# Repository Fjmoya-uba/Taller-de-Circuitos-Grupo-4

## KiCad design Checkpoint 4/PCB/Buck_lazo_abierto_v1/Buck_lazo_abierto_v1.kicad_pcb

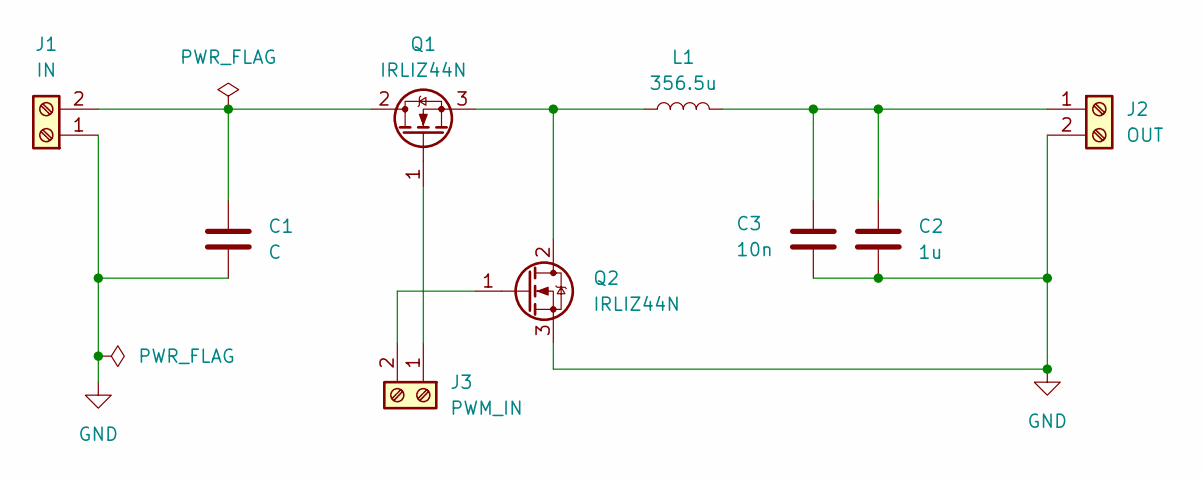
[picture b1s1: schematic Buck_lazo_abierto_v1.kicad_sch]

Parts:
C1: C; C_Radial_D12.5mm_H20.0mm_P5.00mm
C2: 1u; C_Radial_D12.5mm_H20.0mm_P5.00mm
C3: 10n; C_Disc_D10.0mm_W2.5mm_P5.00mm
J1: IN; TerminalBlock_MaiXu_MX126-5.0-02P_1x02_P5.00mm
J2: OUT; TerminalBlock_MaiXu_MX126-5.0-02P_1x02_P5.00mm
J3: PWM_IN; TerminalBlock_MaiXu_MX126-5.0-02P_1x02_P5.00mm
L1: 356.5u; L_Toroid_Vertical_L46.0mm_W19.1mm_P21.80mm_Bourns_5700
Q1, Q2: IRLIZ44N; TO-220F-3_Vertical

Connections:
GND: C1.2, C2.2, C3.2, J1.1, J2.2, Q2.3 (S)
unnamed: C1.1, J1.2, Q1.2 (D)
unnamed: C2.1, C3.1, J2.1, L1.2
unnamed: J3.1, Q1.1 (G)
unnamed: J3.2, Q2.1 (G)
unnamed: L1.1, Q1.3 (S), Q2.2 (D)

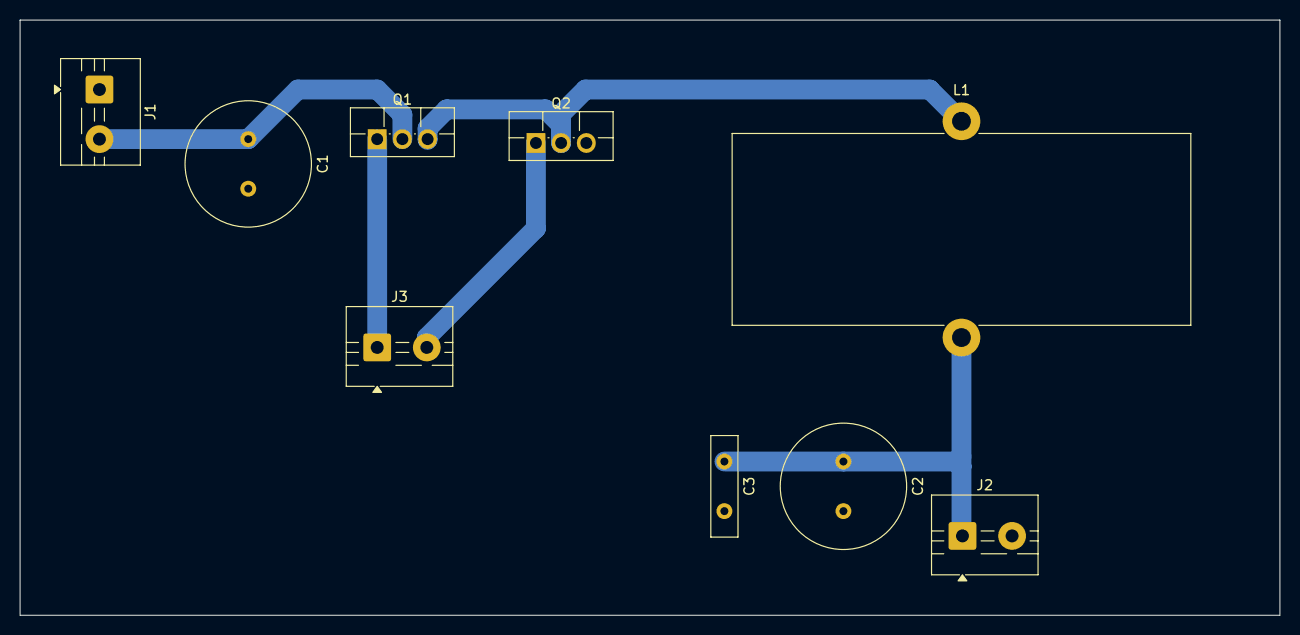
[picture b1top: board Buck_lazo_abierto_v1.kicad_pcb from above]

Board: 2 copper layers, 127.0 x 60.0 mm, 9 parts (0 on the bottom side), 6 nets.

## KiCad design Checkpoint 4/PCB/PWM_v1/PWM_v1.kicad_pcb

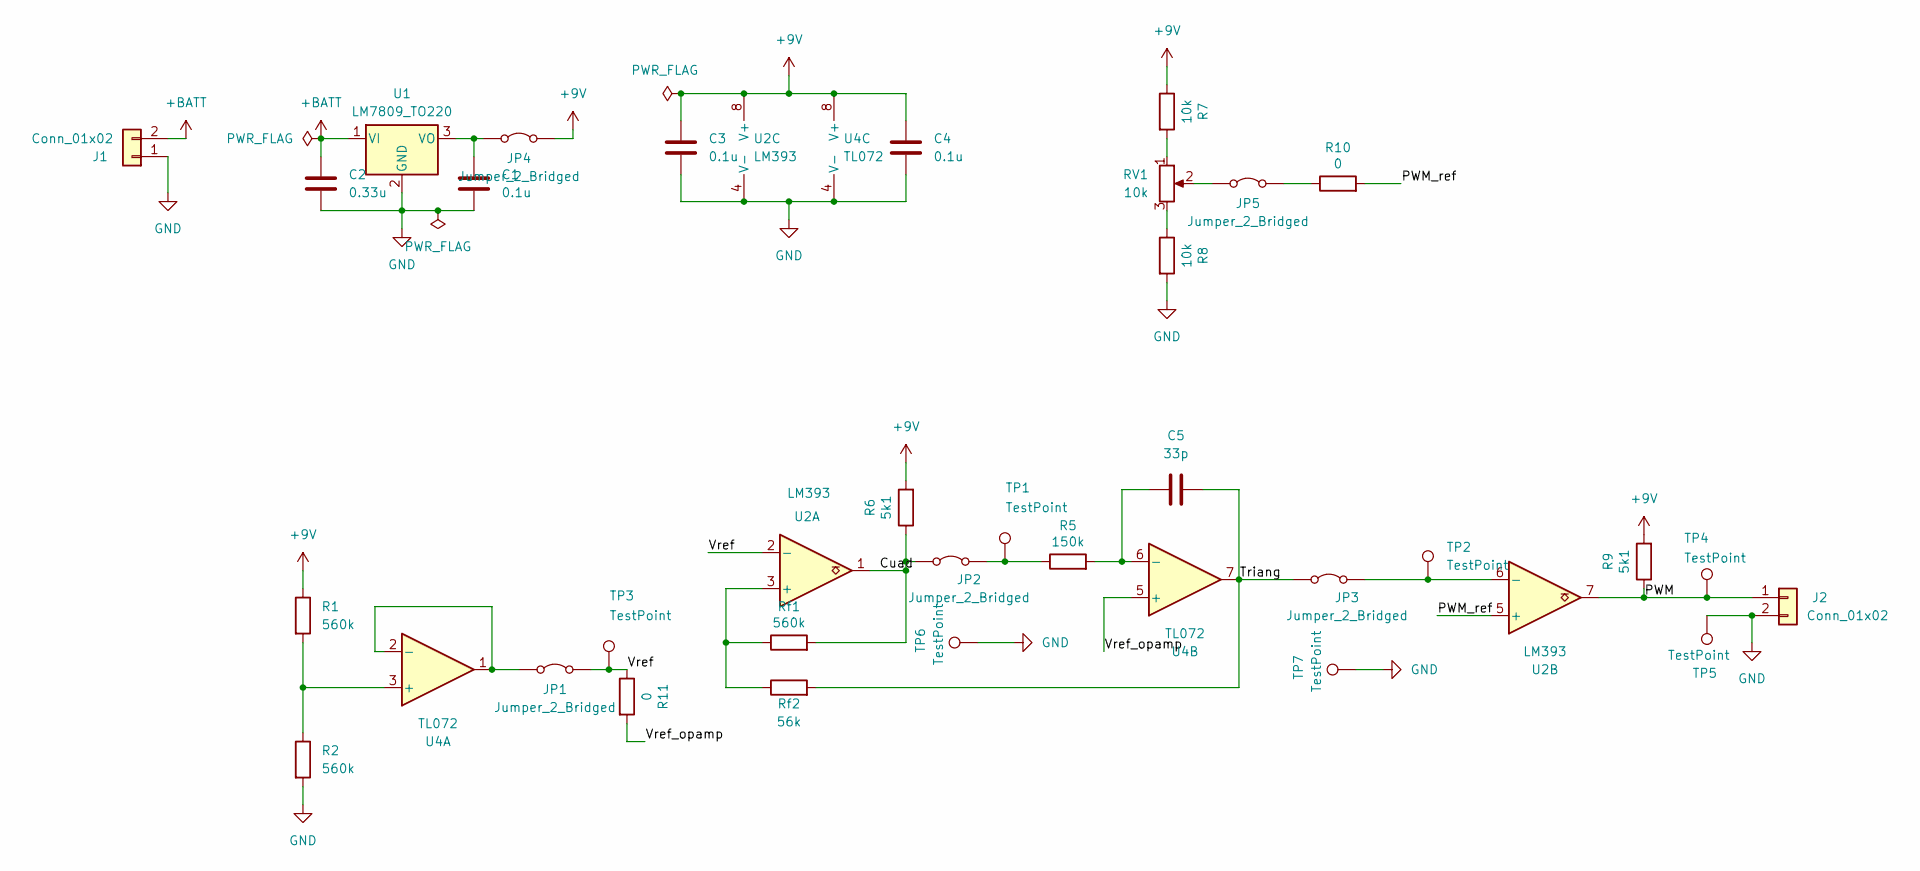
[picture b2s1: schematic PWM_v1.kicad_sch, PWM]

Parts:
C1, C3, C4: 0.1u; C_Disc_D5.0mm_W2.5mm_P2.50mm
C2: 0.33u; C_Disc_D5.0mm_W2.5mm_P2.50mm
C5: 33p; C_Disc_D5.0mm_W2.5mm_P2.50mm
J1, J2: Conn_01x02; TerminalBlock_MaiXu_MX126-5.0-02P_1x02_P5.00mm
JP1, JP2, JP3, JP4, JP5: Jumper_2_Bridged; PinHeader_1x02_P2.54mm_Vertical
R1, R2: 560k; R_Axial_DIN0207_L6.3mm_D2.5mm_P7.62mm_Horizontal
R5: 150k; R_Axial_DIN0207_L6.3mm_D2.5mm_P7.62mm_Horizontal
R6, R9: 5k1; R_Axial_DIN0207_L6.3mm_D2.5mm_P7.62mm_Horizontal
R7, R8: 10k; R_Axial_DIN0207_L6.3mm_D2.5mm_P7.62mm_Horizontal
R10, R11: 0; R_Axial_DIN0207_L6.3mm_D2.5mm_P7.62mm_Horizontal
RV1: 10k; Potentiometer_Piher_PC-16_Single_Horizontal
Rf1: 560k; R_Axial_DIN0207_L6.3mm_D2.5mm_P7.62mm_Horizontal
Rf2: 56k; R_Axial_DIN0207_L6.3mm_D2.5mm_P7.62mm_Horizontal
TP1, TP2, TP3: TestPoint
TP4, TP5, TP6, TP7: TestPoint; PinHeader_1x01_P2.54mm_Vertical
U1: LM7809_TO220; TO-220-3_Vertical
U2: LM393; DIP-8_W7.62mm_Socket_LongPads
U4: TL072; DIP-8_W7.62mm_Socket_LongPads

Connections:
+9V: C3.1, C4.1, JP4.2 (B), R1.1, R6.2, R7.1, R9.2, U2.8 (V+), U4.8 (V+)
+BATT: C2.1, J1.2, U1.1 (VI)
/Cuad: JP2.1 (A), R6.1, Rf1.2, U2.1
/PWM: J2.1, R9.1, TP4.1 (1_1), U2.7
/PWM_ref: R10.2, U2.5 (+)
/Triang: C5.1, JP3.1 (A), Rf2.2, U4.7
/Vref: JP1.2 (B), R11.1, TP3.1, U2.2 (-)
/Vref_opamp: R11.2, U4.5 (+)
GND: C1.2, C2.2, C3.2, C4.2, J1.1, J2.2, R2.2, R8.2, TP5.1 (1_1), TP6.1 (1_1), TP7.1 (1_1), U1.2 (GND), U2.4 (V-), U4.4 (V-)
unnamed: JP1.1 (A), U4.1, U4.2 (-)
unnamed: JP2.2 (B), R5.1, TP1.1
unnamed: JP3.2 (B), TP2.1, U2.6 (-)
unnamed: C1.1, JP4.1 (A), U1.3 (VO)
unnamed: JP5.1 (A), RV1.2
unnamed: JP5.2 (B), R10.1
unnamed: R7.2, RV1.1
unnamed: R8.1, RV1.3
unnamed: Rf1.1, Rf2.1, U2.3 (+)
unnamed: R1.2, R2.1, U4.3 (+)
unnamed: C5.2, R5.2, U4.6 (-)

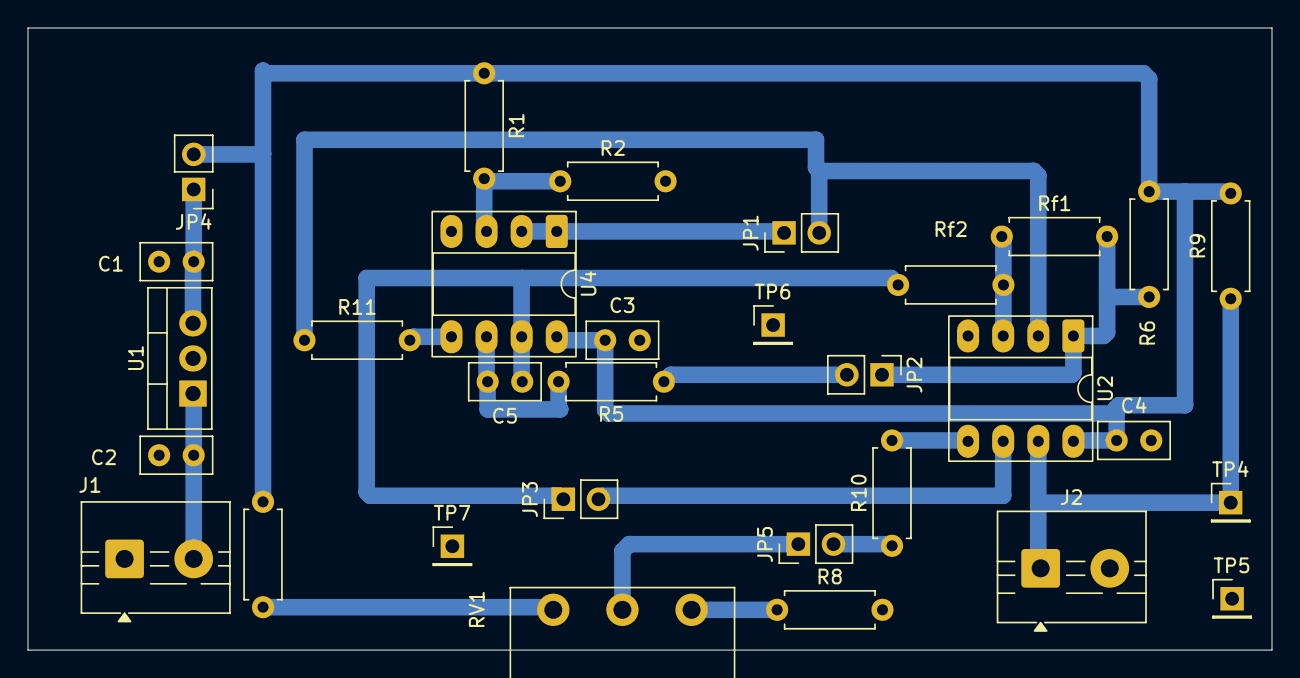
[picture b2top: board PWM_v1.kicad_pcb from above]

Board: 2 copper layers, 90.0 x 45.0 mm, 31 parts (0 on the bottom side), 20 nets.

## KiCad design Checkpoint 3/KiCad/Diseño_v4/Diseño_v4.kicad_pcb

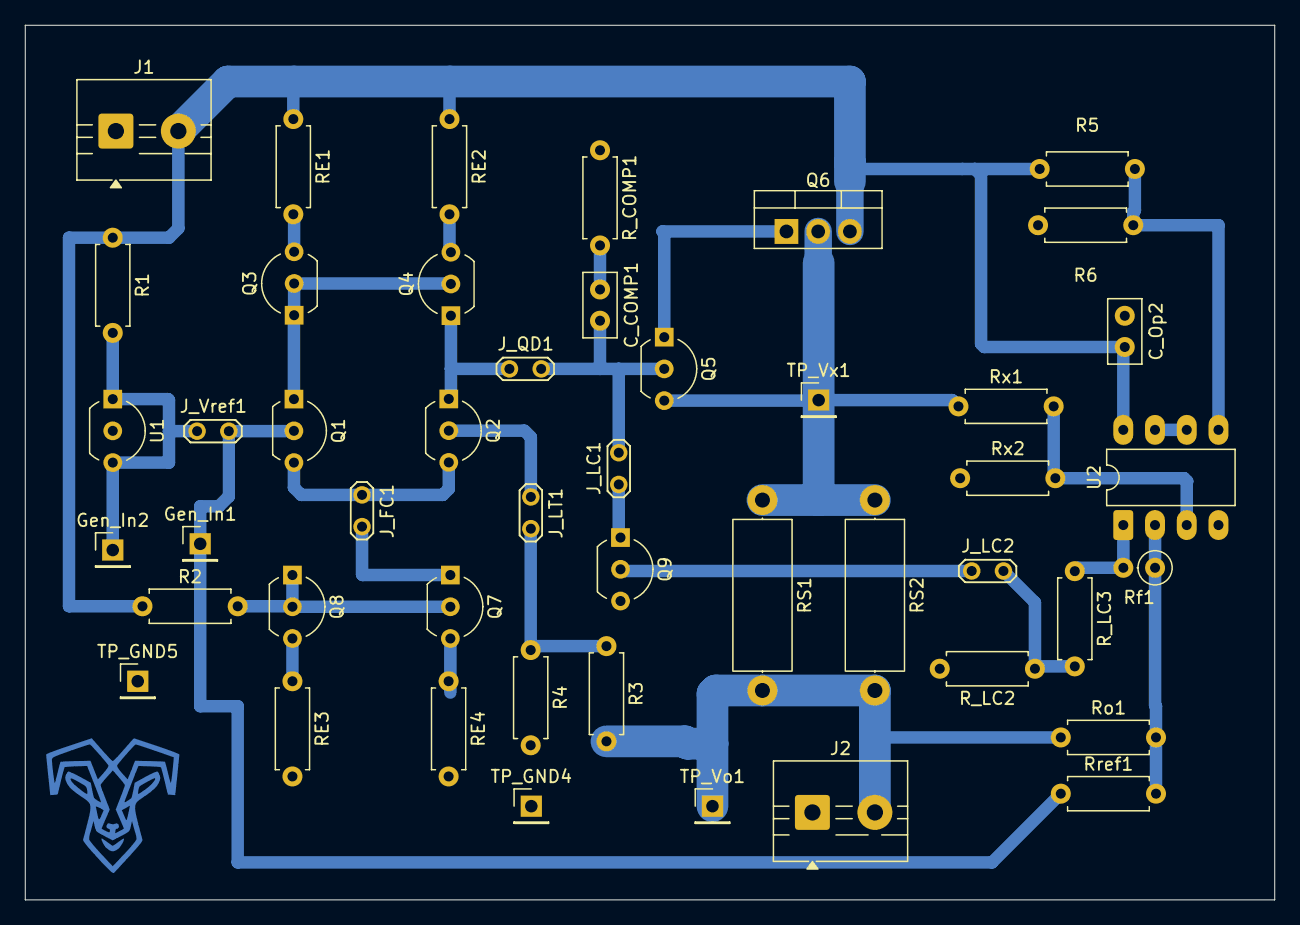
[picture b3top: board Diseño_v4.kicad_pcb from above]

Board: 2 copper layers, 100.0 x 70.0 mm, 47 parts (0 on the bottom side), 28 nets.

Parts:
C_COMP1: 330n; C_Disc_D5.0mm_W2.5mm_P2.50mm
C_Op2: 0.1u; C_Disc_D5.0mm_W2.5mm_P2.50mm
Gen_In1, Gen_In2: PinHeader_1x01_P2.54mm_Vertical
J1, J2: Conn_01x02; TerminalBlock_MaiXu_MX126-5.0-02P_1x02_P5.00mm
J_FC1: TestPoint_2Pads_Pitch2.54mm_Drill0.8mm
J_LC1, J_LC2: TestPoint_2Pads_Pitch2.54mm_Drill0.8mm
J_LT1: TestPoint_2Pads_Pitch2.54mm_Drill0.8mm
J_QD1: TestPoint_2Pads_Pitch2.54mm_Drill0.8mm
J_Vref1: TestPoint_2Pads_Pitch2.54mm_Drill0.8mm
Q1: BC547; TO-92L_Inline_Wide
Q2, Q5, Q7, Q8, Q9: BC547; TO-92_Inline_Wide
Q3, Q4: BC557; TO-92_Inline_Wide
Q6: TIP32A; TO-220-3_Vertical
R1: 680; R_Axial_DIN0207_L6.3mm_D2.5mm_P7.62mm_Horizontal
R2: 4k7; R_Axial_DIN0207_L6.3mm_D2.5mm_P7.62mm_Horizontal
R3, R4: 10k; R_Axial_DIN0207_L6.3mm_D2.5mm_P7.62mm_Horizontal
R5, R6: 1Meg; R_Axial_DIN0207_L6.3mm_D2.5mm_P7.62mm_Horizontal
RE1, RE2, RE3, RE4: 100; R_Axial_DIN0207_L6.3mm_D2.5mm_P7.62mm_Horizontal
RS1: 1.8; R_Axial_DIN0414_L11.9mm_D4.5mm_P15.24mm_Horizontal
RS2: 2.2; R_Axial_DIN0414_L11.9mm_D4.5mm_P15.24mm_Horizontal
R_COMP1: 22; R_Axial_DIN0207_L6.3mm_D2.5mm_P7.62mm_Horizontal
R_LC2: 1k; R_Axial_DIN0207_L6.3mm_D2.5mm_P7.62mm_Horizontal
R_LC3: 3k9; R_Axial_DIN0207_L6.3mm_D2.5mm_P7.62mm_Horizontal
Rf1: 10k; R_Axial_DIN0207_L6.3mm_D2.5mm_P2.54mm_Vertical
Ro1: 150; R_Axial_DIN0207_L6.3mm_D2.5mm_P7.62mm_Horizontal
Rref1: 1k2; R_Axial_DIN0207_L6.3mm_D2.5mm_P7.62mm_Horizontal
Rx1: 3k9; R_Axial_DIN0207_L6.3mm_D2.5mm_P7.62mm_Horizontal
Rx2: 10k; R_Axial_DIN0207_L6.3mm_D2.5mm_P7.62mm_Horizontal
TP_GND4, TP_GND5: PinHeader_1x01_P2.54mm_Vertical
TP_Vo1: PinHeader_1x01_P2.54mm_Vertical
TP_Vx1: PinHeader_1x01_P2.54mm_Vertical
U1: TL431LP; TO-92_Inline_Wide
U2: LM358; DIP-8_W7.62mm_LongPads

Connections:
/Vf: J_LC2.1 (A), Q9.2 (B)
/Vo: J2.2, R3.2, RS1.2, RS2.2, Ro1.1, TP_Vo1.1 (1_1)
/Vref: Gen_In1.1 (1_1), J_Vref1.2 (B), Q1.2 (B), Rref1.1
/Vreg: C_Op2.2, J1.2, Q6.3 (E), R1.1, R2.1, R5.2, RE1.1, RE2.1, U2.8 (V+)
/Vx: Q5.3 (E), Q6.2 (C), RS1.1, RS2.1, Rx1.1, TP_Vx1.1 (1_1)
GND: C_Op2.1, J1.1, J2.1, Q9.3 (E), R4.2, R6.1, RE3.2, RE4.2, R_COMP1.1, R_LC2.2, Rx2.1, TP_GND4.1 (1_1), TP_GND5.1 (1_1), U1.2 (A), U2.4 (V-)
unnamed: C_COMP1.1, R_COMP1.2
unnamed: J_FC1.1 (A), Q1.3 (E), Q2.3 (E)
unnamed: J_FC1.2 (B), Q7.1 (C)
unnamed: J_LC1.1 (A), Q9.1 (C)
unnamed: C_COMP1.2, J_LC1.2 (B), J_QD1.2 (B), Q5.2 (B)
unnamed: J_LC2.2 (B), R_LC2.1, R_LC3.2
unnamed: J_LT1.1 (A), Q2.2 (B)
unnamed: J_LT1.2 (B), R3.1, R4.1
unnamed: J_QD1.1 (A), Q2.1 (C), Q4.1 (C)
unnamed: Gen_In2.1 (1_1), J_Vref1.1 (A), R1.2, U1.1 (REF), U1.3 (K)
unnamed: Q1.1 (C), Q3.1 (C), Q3.2 (B), Q4.2 (B)
unnamed: Q3.3 (E), RE1.2
unnamed: Q4.3 (E), RE2.2
unnamed: Q5.1 (C), Q6.1 (B)
unnamed: Q7.2 (B), Q8.1 (C), Q8.2 (B), R2.2
unnamed: Q7.3 (E), RE4.1
unnamed: Q8.3 (E), RE3.1
unnamed: R_LC3.1, Rf1.2, U2.1
unnamed: Rx1.2, Rx2.2, U2.3 (+)
unnamed: Rf1.1, Ro1.2, Rref1.2, U2.2 (-)
unnamed: R5.1, R6.2, U2.5 (+)
unnamed: U2.6 (-), U2.7

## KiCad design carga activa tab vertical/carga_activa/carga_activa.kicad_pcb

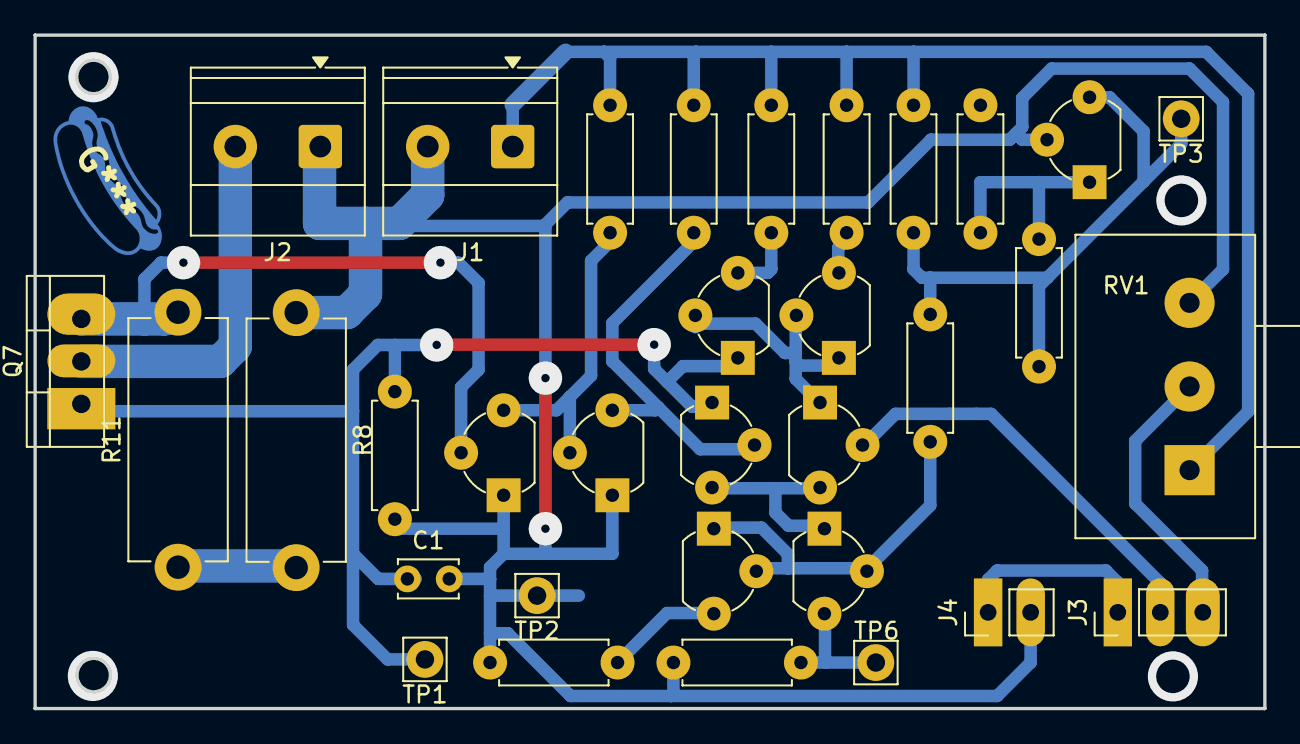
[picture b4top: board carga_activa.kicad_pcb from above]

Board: 2 copper layers, 73.5 x 40.2 mm, 33 parts (0 on the bottom side), 20 nets.

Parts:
C1: 100n; C_Disc_D3.4mm_W2.1mm_P2.50mm
J1, J2: Screw_Terminal_01x02; TerminalBlock_Phoenix_MKDS-1,5-2-5.08_1x02_P5.08mm_Horizont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
J3: Conn_01x03_Pin; PinHeader_1x03_P2.54mm_Vertical
J4: Conn_01x02_Pin; PinHeader_1x02_P2.54mm_Vertical
Q1, Q2, Q4, Q6: BC547; Custom_TO-92_Wide
Q3, Q5, Q8, Q9: BC557; Custom_TO-92_Wide
Q7: IRFZ46; TO-220-3_Vertical
R1, R3: 2k; Custom _pads_R_Axial_DIN0207_L6.3mm_D2.5mm_P7.62mm_Horizont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
R2, R4: 1k; Custom _pads_R_Axial_DIN0207_L6.3mm_D2.5mm_P7.62mm_Horizont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
R5, R7: 100; Custom _pads_R_Axial_DIN0207_L6.3mm_D2.5mm_P7.62mm_Horizont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
R6: 470; Custom _pads_R_Axial_DIN0207_L6.3mm_D2.5mm_P7.62mm_Horizont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
R8, R11: 1; R_Axial_DIN0614_L14.3mm_D5.7mm_P15.24mm_Horizontal
R10: 5k6; Custom _pads_R_Axial_DIN0207_L6.3mm_D2.5mm_P7.62mm_Horizont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
R12: 6k2; Custom _pads_R_Axial_DIN0207_L6.3mm_D2.5mm_P7.62mm_Horizont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
R14: DNP; Custom _pads_R_Axial_DIN0207_L6.3mm_D2.5mm_P7.62mm_Horizont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
R15: 1M; Custom _pads_R_Axial_DIN0207_L6.3mm_D2.5mm_P7.62mm_Horizont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
RV1: 2k; Potentiometer_Alps_RK163_Single_Horizontal
TP1, TP2, TP3, TP6: TestPoint; Pin_D1.1mm_L8.5mm_W2.5mm_FlatFork
U1: TL431LP; Custom_TO-92_Wide

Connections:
/Amp_in: Q6.2 (B), Q9.3 (E), R10.1
/Amp_out: C1.1, Q5.1 (C), Q6.1 (C), Q7.1 (G), R15.1, TP1.1
/V_in: J1.1, R2.2, R5.2, R7.2, R10.2, R12.2, RV1.1
/V_ref: R1.2, R2.1, R3.2, TP3.1, U1.3 (K)
/load_in: J2.2, Q7.2 (D)
/pot_out: J3.2, Q2.2 (B)
/sense_out: Q7.3 (S), Q8.2 (B), R11.2
GND: C1.2, J1.2, J2.1, J4.2, Q8.1 (C), Q9.1 (C), R4.1, R6.1, R8.1, R14.1, R15.2, RV1.3, TP2.1, U1.2 (A)
unnamed: J3.1, J4.1
unnamed: J3.3, RV1.2
unnamed: Q1.1 (C), Q1.2 (B), Q4.2 (B), R3.1
unnamed: Q1.3 (E), R4.2
unnamed: Q2.1 (C), Q3.1 (C), Q3.2 (B), Q5.2 (B)
unnamed: Q2.3 (E), Q4.1 (C), Q6.3 (E)
unnamed: Q3.3 (E), R5.1
unnamed: Q4.3 (E), R6.2, TP6.1
unnamed: Q5.3 (E), R7.1
unnamed: Q8.3 (E), Q9.2 (B), R12.1
unnamed: R8.2, R11.1
unnamed: R1.1, R14.2, U1.1 (REF)

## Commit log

2026-03-28 re-ordenando el repo
2026-03-28 todos los transistores son iguales
2026-04-04 buscando el foldback
2026-04-04 Agrego mis simulaciones
2026-04-07 Foldback con un solo opamp
2026-04-08 Cambié los transistores SMD por unos THT
2026-04-08 kicad 1
2026-04-09 reza malena
2026-04-10 new changes
2026-04-12 Primer commit LGV
2026-04-12 Agrero .tex e /img
2026-04-12 Agrego .pptx
2026-04-16 Prueba branches
2026-04-17 No te voy a mentir, no sé muy bien lo que hice
2026-04-17 NO SOBRE ESCRIBIR ESTOS ARCHIVOS
2026-04-18 con 40n compensa este hijo de puta
2026-04-20 PCB LDO (final?)
2026-04-20 agregué el capacitor de compensación
2026-04-21 Cambié las huellas de los TBJ xq estaban muy juntas
2026-04-22 archivos geber
2026-04-22 Intenté arreglar el lazo de corriente. Fracasé
2026-04-22 pequeño cambio
2026-04-23 viendo cosas
2026-04-23 Corregí el lazo de corriente.
2026-04-23 Corregí el esquemático y generé los archivos de fabricación
2026-04-23 gráficos. Ahora es inestable el lazo de corriente
2026-04-23 no sé por qué esto anda
2026-04-24 Datasheet del Disipador
2026-04-24 COMPENSÓ
2026-04-24 Actualicé el PCB
2026-04-24 archivos gerber
2026-04-24 Informe 2
2026-04-25 No sé qué toqué
2026-04-25 lista de materiales
2026-04-26 Corrección PCB
2026-04-26 últimos retoques al PCB
2026-04-27 Archivos .gbr
2026-05-02 checkpoint 3
2026-05-05 una simulación y pcb
2026-05-05 Simulación de la regulación de carga dinámica
2026-05-06 Probé un par de cosas sin mucho éxito
2026-05-06 Arreglando la placa
2026-05-07 no anda nada loco
2026-05-08 Carga electrónica
2026-05-08 gráfico regulación de linea
2026-05-08 agregué la hoja de datos del nmos (IRFZ46N)
2026-05-08 Modif. Reg_Lin
2026-05-08 Modif. Reg_Lin 2
2026-05-08 Modif. Reg_Lin 3
2026-05-08 cambios del pcb
2026-05-08 quince commits en el mismo día
2026-05-09 Rename main.tex to checkpoint1/2.tex
    Rename main.tex to checkpoint2.tex in Checkpoint 2/Informe and to checkpoint1.tex in Ckeckpoint 1/Informe. Both files are identical (100% similarity); this change only updates filenames for clearer c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
2026-05-09 Salió todo sobre la hora
2026-05-09 Imágenes varias - Modif. script Python
2026-05-10 Agrego Informe y Modif. Datasheets
2026-05-11 agregué la cabrita al pcb
2026-05-21 checkpoint 4
2026-05-22 Avances TP2
2026-05-23 avances chpoint4
2026-05-25 Buck-converter funcionando en ltspice
2026-05-25 Hojas de datos
2026-05-25 datasheet regulador
2026-05-25 Update in this schematics
2026-05-25 simulación
2026-05-25 Erickson
2026-05-26 PCB PWM
2026-05-26 Cambié el TL062 por el TL072
2026-05-26 modifiqué datasheet del regulador
2026-05-29 cambié un poco la simulación
2026-05-31 simulación pwm
2026-06-01 pcb buck
2026-06-01 Agrego Informe Chck4
